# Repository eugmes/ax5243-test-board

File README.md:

AX5243 Shield for Arduino Nano (3.3V)
=====================================

This is a small test board for AX5243 narrow-band transceiver chip with pinout
compatible with Arduino Nano. Note that the board requires 3.3V supply voltage.

The antenna is matched at 169 MHz. The board is designed using
[KiCad](https://kicad.org), and currently requires a nightly build
(version 5.99). The [schematic](schematic/ax5243-test-board.pdf) is also
available in PDF format. The generated gerber files are available in
[gerbers](gerbers) directory. The board is also available on
[Aisler](https://aisler.net/p/OMGYYSHU) (latest available revision is
[B](https://github.com/eugmes/ax5243-test-board/releases/tag/rev-B)).

The produced board was tested using NUCLEO-L432KC development board
and was able to receive and transmit AIS signals. Some test software is
available here: https://github.com/eugmes/ax5243-zephyr

Changes since last release:

* Added additional matching capacitor that is needed for higher frequencies.

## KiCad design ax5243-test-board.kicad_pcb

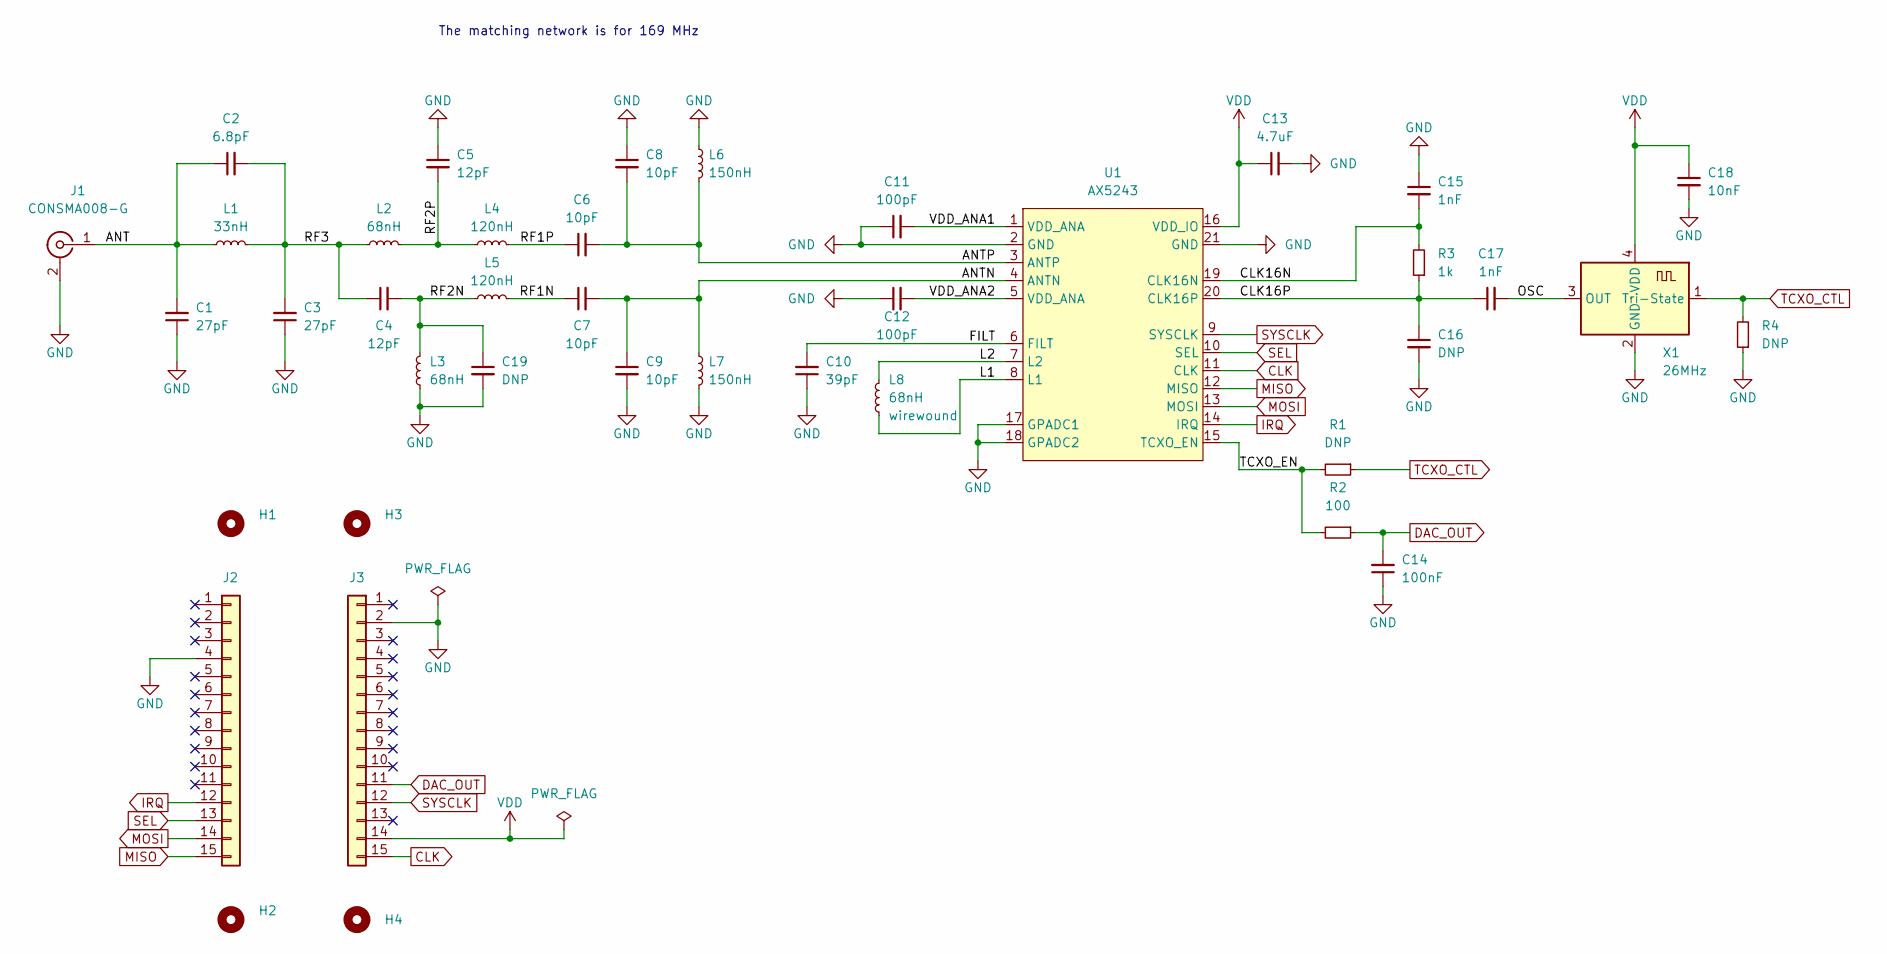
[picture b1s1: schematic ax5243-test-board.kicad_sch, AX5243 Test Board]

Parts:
C1, C3: 27pF; C_0402_1005Metric
C2: 6.8pF; C_0402_1005Metric
C4, C5: 12pF; C_0402_1005Metric
C6, C7, C8, C9: 10pF; C_0402_1005Metric
C10: 39pF; C_0402_1005Metric
C11, C12: 100pF; C_0402_1005Metric
C13: 4.7uF; C_0603_1608Metric
C14: 100nF; C_0402_1005Metric
C15, C17: 1nF; C_0402_1005Metric
C16, C19: DNP; C_0402_1005Metric
C18: 10nF; C_0402_1005Metric
H1, H2, H3, H4: MountingHole; MountingHole_1.8mm
J1: CONSMA008-G; SMA_Amphenol_132291-12_Vertical
J2, J3: Conn_01x15; PinSocket_1x15_P2.54mm_Vertical
L1: 33nH; L_0402_1005Metric
L2, L3: 68nH; L_0402_1005Metric
L4, L5: 120nH; L_0402_1005Metric
L6, L7: 150nH; L_0603_1608Metric
L8: 68nH; L_0603_1608Metric; Rating wirewound
R1, R4: DNP; R_0402_1005Metric
R2: 100; R_0402_1005Metric
R3: 1k; R_0402_1005Metric
U1: AX5243; QFN50P400X400X80-21B-THERMALVIAS
X1: 26MHz; Oscillator_SMD_Abracon_ASDMB-4Pin_2.5x2.0mm

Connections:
/ANT: C1.2, C2.1, J1.1 (In), L1.1
/ANTN: C7.2, C9.1, L7.1, U1.4 (ANTN)
/ANTP: C6.2, C8.2, L6.2, U1.3 (ANTP)
/CLK16N: C15.2, R3.2, U1.19 (CLK16N)
/CLK16P: C16.1, C17.1, R3.1, U1.20 (CLK16P)
/FILT: C10.2, U1.6 (FILT)
/L1: L8.1, U1.8 (L1)
/L2: L8.2, U1.7 (L2)
/OSC: C17.2, X1.3 (OUT)
/RF1N: C7.1, L5.2
/RF1P: C6.1, L4.2
/RF2N: C4.2, C19.1, L3.2, L5.1
/RF2P: C5.2, L2.2, L4.1
/RF3: C2.2, C3.2, C4.1, L1.2, L2.1
/TCXO_EN: R1.2, R2.2, U1.15 (TCXO_EN)
/VDD_ANA1: C11.2, U1.1 (VDD_ANA)
/VDD_ANA2: C12.2, U1.5 (VDD_ANA)
CLK: J3.15, U1.11 (CLK)
DAC_OUT: C14.2, J3.11, R2.1
GND: C1.1, C3.1, C5.1, C8.1, C9.2, C10.1, C11.1, C12.1, C13.2, C14.1, C15.1, C16.2, C18.2, C19.2, J1.2 (Ext), J2.4, J3.2, L3.1, L6.1, L7.2, R4.1, U1.2 (GND), U1.17 (GPADC1), U1.18 (GPADC2), U1.21 (GND), X1.2 (GND)
IRQ: J2.12, U1.14 (IRQ)
MISO: J2.15, U1.12 (MISO)
MOSI: J2.14, U1.13 (MOSI)
SEL: J2.13, U1.10 (SEL)
SYSCLK: J3.12, U1.9 (SYSCLK)
TCXO_CTL: R1.1, R4.2, X1.1 (Tri-State)
VDD: C13.1, C18.1, J3.14, U1.16 (VDD_IO), X1.4 (VDD)

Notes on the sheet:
The matching network is for 169 MHz

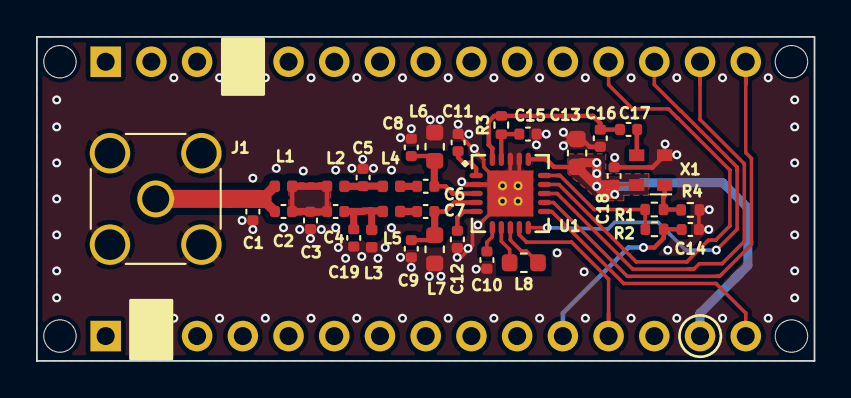
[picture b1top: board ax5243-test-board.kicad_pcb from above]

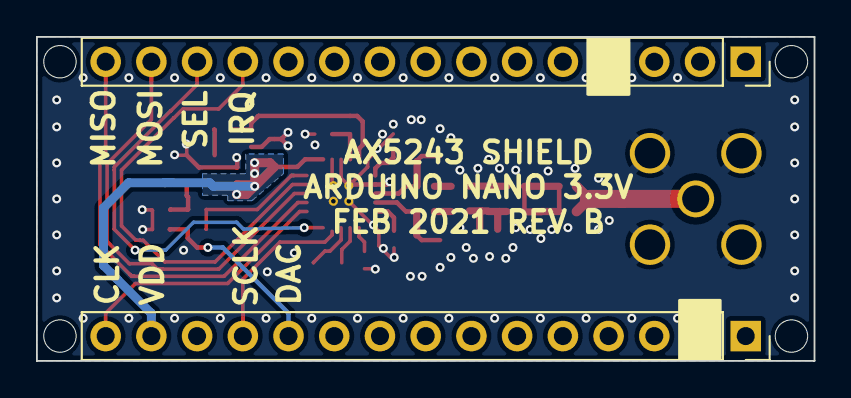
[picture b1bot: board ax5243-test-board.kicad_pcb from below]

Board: 2 copper layers, 43.2 x 18.0 mm, 40 parts (2 on the bottom side), 27 nets.

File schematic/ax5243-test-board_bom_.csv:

References,Value,Footprint,Quantity Per PCB,MFT Name,MFT Number,Vendor,SKU,Config,Rating
C14,100nF,C_0402_1005Metric,1,Murata,GRM155R71H104KE14D,Digikey,490-10700-1-ND,,
C11 C12,100pF,C_0402_1005Metric,2,Murata,GCM1555C1H101GA16D,Digikey,490-GCM1555C1H101GA16DCT-ND,,
C18,10nF,C_0402_1005Metric,1,Murata,GRM155R71H103KA88J,Digikey,490-6351-1-ND,,
C6 C7 C8 C9,10pF,C_0402_1005Metric,4,Murata,GJM1555C1H100FB01D,Digikey,490-11189-1-ND,,
C4 C5,12pF,C_0402_1005Metric,2,Murata,GJM1555C1H120JB01D,Digikey,490-3115-1-ND,,
C15 C17,1nF,C_0402_1005Metric,2,Murata,GRM1555C1H102GA01D,Digikey,490-8181-1-ND,,
C1 C3,27pF,C_0402_1005Metric,2,Murata,GJM1555C1H270FB01D,Digikey,490-16380-1-ND,,
C10,39pF,C_0402_1005Metric,1,Murata,GJM1555C1H390JB01D,Digikey,490-17673-1-ND,,
C13,4.7uF,C_0603_1608Metric,1,Murata,GRM188R61E475KE11D,Digikey,490-7203-1-ND,,
C2,6.8pF,C_0402_1005Metric,1,Murata,GJM1555C1H6R8CB01D,Digikey,490-3106-1-ND,,
J1,CONSMA008-G,SMA_Amphenol_132291-12_Vertical,1,Linx Technologies,CONSMA008-G,Digikey,CONSMA008-G-ND,,
J2 J3,Conn_01x15,PinSocket_1x15_P2.54mm_Vertical,2,Harwin,M20-7821546,Digikey,952-2290-ND,,
L4 L5,120nH,L_0402_1005Metric,2,Murata,LQW15ANR12J00D,Digikey,490-4091-1-ND,,
L6 L7,150nH,L_0603_1608Metric,2,Murata,LQW18ANR15J00D,Digikey,490-6924-1-ND,,
L1,33nH,L_0402_1005Metric,1,Murata,LQW15AN33NH00D,Digikey,490-6805-1-ND,,
L2 L3,68nH,L_0402_1005Metric,2,Murata,LQW15AN68NG00D,Digikey,490-6837-1-ND,,
L8,68nH,L_0603_1608Metric,1,Murata,LQW18AN68NG00D,Digikey,490-6904-1-ND,,wirewound
R2,100,R_0402_1005Metric,1,Yageo,RC0402FR-07100RP,Digikey,YAG1248CT-ND,,
R3,1k,R_0402_1005Metric,1,Yageo,RC0402FR-071KP,Digikey,YAG1254CT-ND,,
U1,AX5243,QFN50P400X400X80-21B-THERMALVIAS,1,ON Semiconductor,AX5243-1-TW30,Digikey,488-AX5243-1-TW30CT-ND,,
X1,26MHz,Oscillator_SMD_Abracon_ASDMB-4Pin_2.5x2.0mm,1,Taitien,TYETACSANF-26.000000,Digikey,1664-1297-1-ND,,0.5ppm

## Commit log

2021-01-19 Add gerbers for ordered board
2021-01-19 Add schematic plot
2021-01-22 Add .gitignore and remove kicad_prl file from the repo
2021-01-27 Add KiBoM config file
2021-01-27 Add part numbers and Digikey SKUs
    Also change TCXO frequency to 26 MHz.
2021-01-27 Rename schematic and gerbers directories
2021-01-27 Don't ignore CSV files
2021-01-27 Add BOM file
2021-01-27 Add README.md
2021-01-27 Add board rendering
2021-01-27 Correct the link to the schematic
2021-01-27 Remove footer from the BOM file
2021-02-02 Move the extension connections to the correct location
    Add solder mask extension.
2021-02-15 New kicad nigtly version
2021-02-15 Update production files
2021-02-15 Update the 3D rendering
2021-05-19 Add component placement files
    This file is completely unverified. Closes: #2.
2021-05-19 Regenerate the placement file
    Don't use "Exclude all footprints with through hole pads" this time, so
    that the trnsceiver chip is not excluded. Really closes: #2.
2021-05-19 Update the README stating that the board is working
2021-05-19 Add additional matching capacitor needed for higher frequencies
    This closes: #3
2021-05-19 Fix a link
